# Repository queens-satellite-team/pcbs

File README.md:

# QSAT PCB Files

## Overview
This README contains information on how to setup your KiCad 6.0 environment. It includes:
1. How to use the existing schematic symbols and layout footprints
2. How to start a new project from an existing template
3. How to prepare the manufacturing and assembly files for ordering from JLCPCB

## Using QSAT PCB Symbols and Footprints

Following the instructions provided here: [How to Import into KiCad v6](https://support.snapeda.com/en/articles/5995733-how-to-import-into-kicad-v6-later)

**Import Symbols**

1. In KiCad, go to Preferences.

2. Click on Manage Symbol Libraries.

3. On the Global Libraries tab, click on Browse Libraries (the small folder icon below) 

4. Select the .lib file, then click Open. 

5. The library will appear, click OK.

6. Click on Symbol Editor.

7. Type on the filter search field, and navigate to the symbol you imported. Double-click over it to open the file.

**Import Footprints**

Using the *.kicad_mod file:

1. In KiCad, go to Preferences.

2. Click on Manage Footprint Libraries.

3. On the Global Libraries tab, click on Browse Libraries (the small folder icon below) 

4. Navigate to the Folder of the downloaded .kicad_mod file. Then click Select Folder. 

5. The library will appear, click OK. 

6. Click on Footprint Editor.

7. Type on the filter search field, and navigate to the footprint you imported. Double-click over it to open the file.

## Using QSAT PCB Templates

Following the instructions provided here: [KiCad Creating Templates](https://docs.kicad.org/5.1/en/kicad/kicad.html#creating_templates) we must:

1. Update our path configurations in KiCad to include the template folder.

a. Go to *Preferences* -> *Configure Paths* in the KiCad GUI.

b. Go to *KICAD_USER_TEMPLATE_DIR* and double click the path name until a folder apprears. 

c. Navigate to the *QSAT/pcbs/qsat-templates* directory and hit *Select Folder*

2. Create a new project from the template. 

a. Go to *File* -> *New Project From Template...* in the KiCad GUI.

b. Select the *User Templates* tab, and choose the template you want. 

**Note:** If starting a project from scratch it is recommended to use the *QSAT - PC104 Base Board* 
This is designed to have the same pcb footprint as the Clyde Space EPS board with mounting holes and
a PC104 connector.

## Ordering From JLCPCB

JLC has provided instructions for their required procedure, and is well detailed. 

The steps to generate the manufacturing files are found [here](https://support.jlcpcb.com/article/194-how-to-generate-gerber-and-drill-files-in-kicad-6). 

And the steps to generate the BOM and Centroid files are found [here](https://support.jlcpcb.com/article/84-how-to-generate-the-bom-and-centroid-file-from-kicad).

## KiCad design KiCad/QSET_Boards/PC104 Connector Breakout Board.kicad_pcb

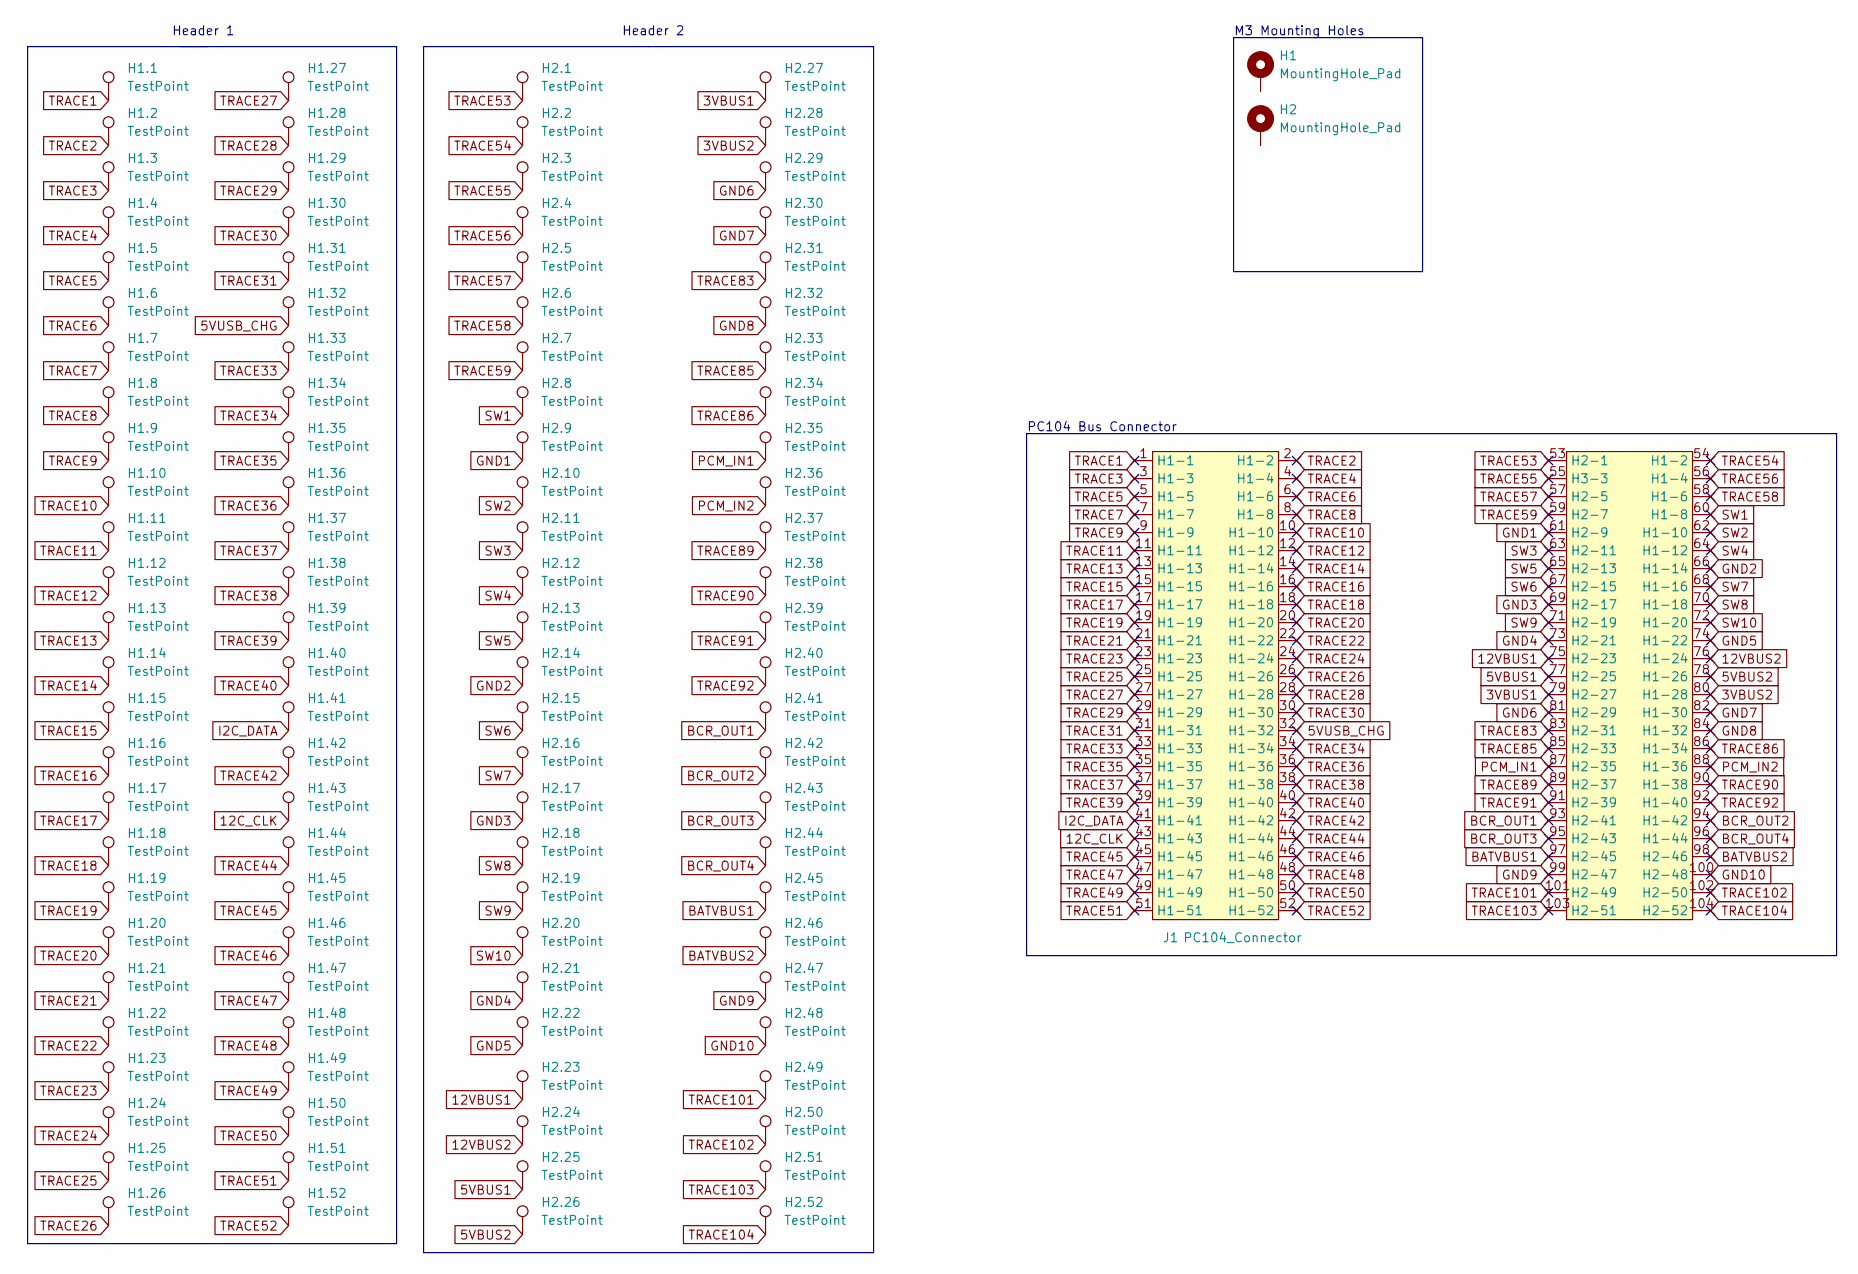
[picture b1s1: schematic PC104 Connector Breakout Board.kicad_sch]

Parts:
H1, H2: MountingHole_Pad; MountingHole_3.2mm_M3_Pad_TopBottom
H1.1, H1.2, H1.3, H1.4, H1.5, H1.6, H1.7, H1.8, H1.9, H1.10, H1.11, H1.12, H1.13, H1.14, H1.15, H1.16, H1.17, H1.18, H1.19, H1.20, H1.21, H1.22, H1.23, H1.24, H1.25, H1.26, H1.27, H1.28, H1.29, H1.30, H1.31, H1.32, H1.33, H1.34, H1.35, H1.36, H1.37, H1.38, H1.39, H1.40, H1.41, H1.42, H1.43, H1.44, H1.45, H1.46, H1.47, H1.48, H1.49, H1.50, H1.51, H1.52, H2.1, H2.2, H2.3, H2.4, H2.5, H2.6, H2.7, H2.8, H2.9, H2.10, H2.11, H2.12, H2.13, H2.14, H2.15, H2.16, H2.17, H2.18, H2.19, H2.20, H2.21, H2.22, H2.23, H2.24, H2.25, H2.26, H2.27, H2.28, H2.29, H2.30, H2.31, H2.32, H2.33, H2.34, H2.35, H2.36, H2.37, H2.38, H2.39, H2.40, H2.41, H2.42, H2.43, H2.44, H2.45, H2.46, H2.47, H2.48, H2.49, H2.50, H2.51, H2.52: TestPoint; TestPoint_Keystone_5000-5004_Miniature
J1: PC104_Connector; pc104-connector

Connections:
3VBUS1: H2.27.1, J1.79 (H2-27)
3VBUS2: H2.28.1, J1.80 (H1-28)
5VBUS1: H2.25.1, J1.77 (H2-25)
5VBUS2: H2.26.1, J1.78 (H1-26)
5VUSB_CHG: H1.32.1, J1.32 (H1-32)
12C_CLK: H1.43.1, J1.43 (H1-43)
12VBUS1: H2.23.1, J1.75 (H2-23)
12VBUS2: H2.24.1, J1.76 (H1-24)
BATVBUS1: H2.45.1, J1.97 (H2-45)
BATVBUS2: H2.46.1, J1.98 (H2-46)
BCR_OUT1: H2.41.1, J1.93 (H2-41)
BCR_OUT2: H2.42.1, J1.94 (H1-42)
BCR_OUT3: H2.43.1, J1.95 (H2-43)
BCR_OUT4: H2.44.1, J1.96 (H1-44)
GND1: H2.9.1, J1.61 (H2-9)
GND2: H2.14.1, J1.66 (H1-14)
GND3: H2.17.1, J1.69 (H2-17)
GND4: H2.21.1, J1.73 (H2-21)
GND5: H2.22.1, J1.74 (H1-22)
GND6: H2.29.1, J1.81 (H2-29)
GND7: H2.30.1, J1.82 (H1-30)
GND8: H2.32.1, J1.84 (H1-32)
GND9: H2.47.1, J1.99 (H2-47)
GND10: H2.48.1, J1.100 (H2-48)
I2C_DATA: H1.41.1, J1.41 (H1-41)
PCM_IN1: H2.35.1, J1.87 (H2-35)
PCM_IN2: H2.36.1, J1.88 (H1-36)
SW1: H2.8.1, J1.60 (H1-8)
SW2: H2.10.1, J1.62 (H1-10)
SW3: H2.11.1, J1.63 (H2-11)
SW4: H2.12.1, J1.64 (H1-12)
SW5: H2.13.1, J1.65 (H2-13)
SW6: H2.15.1, J1.67 (H2-15)
SW7: H2.16.1, J1.68 (H1-16)
SW8: H2.18.1, J1.70 (H1-18)
SW9: H2.19.1, J1.71 (H2-19)
SW10: H2.20.1, J1.72 (H1-20)
TRACE1: H1.1.1, J1.1 (H1-1)
TRACE2: H1.2.1, J1.2 (H1-2)
TRACE3: H1.3.1, J1.3 (H1-3)
TRACE4: H1.4.1, J1.4 (H1-4)
TRACE5: H1.5.1, J1.5 (H1-5)
TRACE6: H1.6.1, J1.6 (H1-6)
TRACE7: H1.7.1, J1.7 (H1-7)
TRACE8: H1.8.1, J1.8 (H1-8)
TRACE9: H1.9.1, J1.9 (H1-9)
TRACE10: H1.10.1, J1.10 (H1-10)
TRACE11: H1.11.1, J1.11 (H1-11)
TRACE12: H1.12.1, J1.12 (H1-12)
TRACE13: H1.13.1, J1.13 (H1-13)
TRACE14: H1.14.1, J1.14 (H1-14)
TRACE15: H1.15.1, J1.15 (H1-15)
TRACE16: H1.16.1, J1.16 (H1-16)
TRACE17: H1.17.1, J1.17 (H1-17)
TRACE18: H1.18.1, J1.18 (H1-18)
TRACE19: H1.19.1, J1.19 (H1-19)
TRACE20: H1.20.1, J1.20 (H1-20)
TRACE21: H1.21.1, J1.21 (H1-21)
TRACE22: H1.22.1, J1.22 (H1-22)
TRACE23: H1.23.1, J1.23 (H1-23)
TRACE24: H1.24.1, J1.24 (H1-24)
TRACE25: H1.25.1, J1.25 (H1-25)
TRACE26: H1.26.1, J1.26 (H1-26)
TRACE27: H1.27.1, J1.27 (H1-27)
TRACE28: H1.28.1, J1.28 (H1-28)
TRACE29: H1.29.1, J1.29 (H1-29)
TRACE30: H1.30.1, J1.30 (H1-30)
TRACE31: H1.31.1, J1.31 (H1-31)
TRACE33: H1.33.1, J1.33 (H1-33)
TRACE34: H1.34.1, J1.34 (H1-34)
TRACE35: H1.35.1, J1.35 (H1-35)
TRACE36: H1.36.1, J1.36 (H1-36)
TRACE37: H1.37.1, J1.37 (H1-37)
TRACE38: H1.38.1, J1.38 (H1-38)
TRACE39: H1.39.1, J1.39 (H1-39)
TRACE40: H1.40.1, J1.40 (H1-40)
TRACE42: H1.42.1, J1.42 (H1-42)
TRACE44: H1.44.1, J1.44 (H1-44)
TRACE45: H1.45.1, J1.45 (H1-45)
TRACE46: H1.46.1, J1.46 (H1-46)
TRACE47: H1.47.1, J1.47 (H1-47)
TRACE48: H1.48.1, J1.48 (H1-48)
TRACE49: H1.49.1, J1.49 (H1-49)
TRACE50: H1.50.1, J1.50 (H1-50)
TRACE51: H1.51.1, J1.51 (H1-51)
TRACE52: H1.52.1, J1.52 (H1-52)
TRACE53: H2.1.1, J1.53 (H2-1)
TRACE54: H2.2.1, J1.54 (H1-2)
TRACE55: H2.3.1, J1.55 (H3-3)
TRACE56: H2.4.1, J1.56 (H1-4)
TRACE57: H2.5.1, J1.57 (H2-5)
TRACE58: H2.6.1, J1.58 (H1-6)
TRACE59: H2.7.1, J1.59 (H2-7)
TRACE83: H2.31.1, J1.83 (H2-31)
TRACE85: H2.33.1, J1.85 (H2-33)
TRACE86: H2.34.1, J1.86 (H1-34)
TRACE89: H2.37.1, J1.89 (H2-37)
TRACE90: H2.38.1, J1.90 (H1-38)
TRACE91: H2.39.1, J1.91 (H2-39)
TRACE92: H2.40.1, J1.92 (H1-40)
TRACE101: H2.49.1, J1.101 (H2-49)
TRACE102: H2.50.1, J1.102 (H2-50)
TRACE103: H2.51.1, J1.103 (H2-51)
TRACE104: H2.52.1, J1.104 (H2-52)

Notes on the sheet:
M3 Mounting Holes
Header 2
Header 1
PC104 Bus Connector

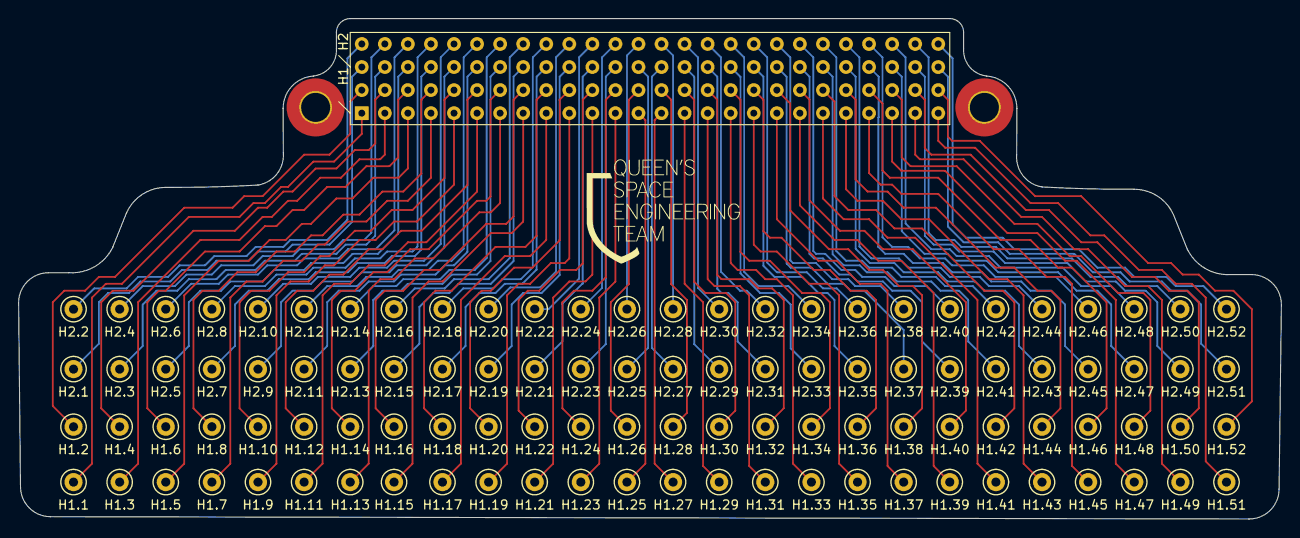
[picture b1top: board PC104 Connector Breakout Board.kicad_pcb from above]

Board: 2 copper layers, 139.1 x 55.1 mm, 107 parts (0 on the bottom side), 104 nets.

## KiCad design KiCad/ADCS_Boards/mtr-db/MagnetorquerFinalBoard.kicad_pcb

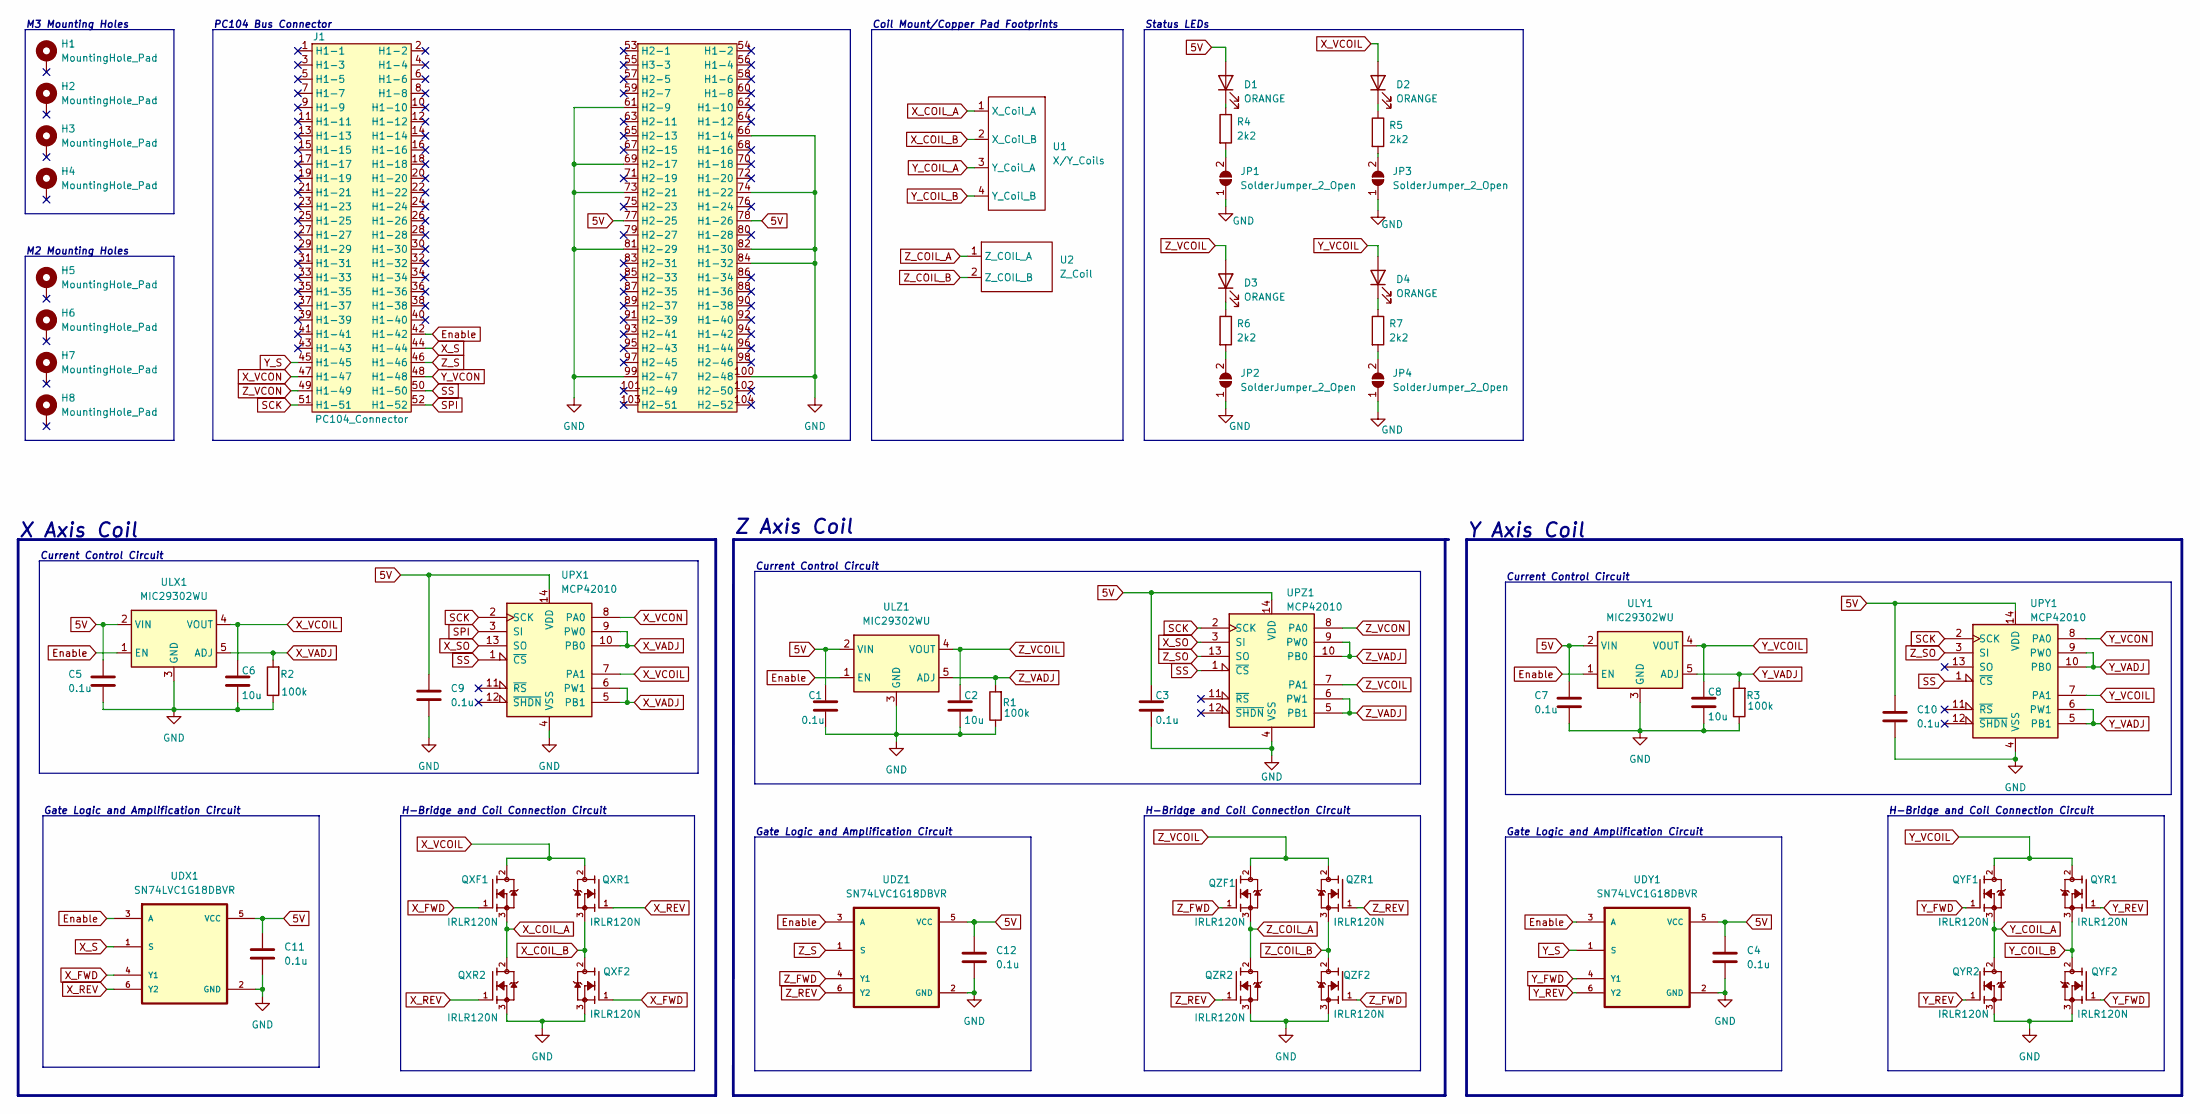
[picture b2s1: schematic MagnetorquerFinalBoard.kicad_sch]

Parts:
C1, C3, C4, C5, C7, C9, C10, C11, C12: 0.1u; C_0603_1608Metric
C2, C6, C8: 10u; C_0603_1608Metric
D1, D2, D3, D4: ORANGE; LED_0603_1608Metric
H1, H2, H3, H4: MountingHole_Pad; MountingHole_3.2mm_M3_Pad_TopBottom
H5, H6, H7, H8: MountingHole_Pad; MountingHole_2.2mm_M2_Pad_TopBottom
J1: PC104_Connector; pc104-connector
JP1, JP2, JP3, JP4: SolderJumper_2_Open; SolderJumper-2_P1.3mm_Open_TrianglePad1.0x1.5mm
QXF1, QXF2: IRLR120N; TO-252-2; PARTREV july 2014
QXR1, QXR2: IRLR120N; TO-252-2; PARTREV july 2014
QYF1, QYF2: IRLR120N; TO-252-2; PARTREV july 2014
QYR1, QYR2: IRLR120N; TO-252-2; PARTREV july 2014
QZF1, QZF2: IRLR120N; TO-252-2; PARTREV july 2014
QZR1, QZR2: IRLR120N; TO-252-2; PARTREV july 2014
R1, R2, R3: 100k; R_0603_1608Metric
R4, R5, R6, R7: 2k2; R_0603_1608Metric
U1: X/Y_Coils; Front Coils Mount
U2: Z_Coil; ZCoil
UDX1: SN74LVC1G18DBVR; SOT95P280X145-6N
UDY1: SN74LVC1G18DBVR; SOT95P280X145-6N
UDZ1: SN74LVC1G18DBVR; SOT95P280X145-6N
ULX1: MIC29302WU; TO-263-5_TabPin3
ULY1: MIC29302WU; TO-263-5_TabPin3
ULZ1: MIC29302WU; TO-263-5_TabPin3
UPX1: MCP42010; SOIC127P600X175-14N
UPY1: MCP42010; SOIC127P600X175-14N
UPZ1: MCP42010; SOIC127P600X175-14N

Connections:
5V: C1.1, C3.1, C4.1, C5.1, C7.1, C9.1, C10.1, C11.1, C12.1, D1.2 (A), J1.77 (H2-25), J1.78 (H1-26), UDX1.5 (VCC), UDY1.5 (VCC), UDZ1.5 (VCC), ULX1.2 (VIN), ULY1.2 (VIN), ULZ1.2 (VIN), UPX1.14 (VDD), UPY1.14 (VDD), UPZ1.14 (VDD)
Enable: J1.42 (H1-42), UDX1.3 (A), UDY1.3 (A), UDZ1.3 (A), ULX1.1 (EN), ULY1.1 (EN), ULZ1.1 (EN)
GND: C1.2, C2.2, C3.2, C4.2, C5.2, C6.2, C7.2, C8.2, C9.2, C10.2, C11.2, C12.2, J1.61 (H2-9), J1.66 (H1-14), J1.69 (H2-17), J1.73 (H2-21), J1.74 (H1-22), J1.81 (H2-29), J1.82 (H1-30), J1.84 (H1-32), J1.99 (H2-47), J1.100 (H2-48), JP1.1 (A), JP2.1 (A), JP3.1 (A), JP4.1 (A), QXF2.3, QXR2.3, QYF2.3, QYR2.3, QZF2.3, QZR2.3, R1.1, R2.1, R3.1, UDX1.2 (GND), UDY1.2 (GND), UDZ1.2 (GND), ULX1.3 (GND), ULY1.3 (GND), ULZ1.3 (GND), UPX1.4 (VSS), UPY1.4 (VSS), UPZ1.4 (VSS)
unnamed: D1.1 (K), R4.1
unnamed: D2.1 (K), R5.1
unnamed: D3.1 (K), R6.1
unnamed: D4.1 (K), R7.1
unnamed: JP1.2 (B), R4.2
unnamed: JP3.2 (B), R5.2
unnamed: JP2.2 (B), R6.2
unnamed: JP4.2 (B), R7.2
SCK: J1.51 (H1-51), UPX1.2 (SCK), UPY1.2 (SCK), UPZ1.2 (SCK)
SPI: J1.52 (H1-52), UPX1.3 (SI)
SS: J1.50 (H1-50), UPX1.1 (~CS), UPY1.1 (~CS), UPZ1.1 (~CS)
X_COIL_A: QXF1.3, QXR2.2, U1.1 (X_Coil_A)
X_COIL_B: QXF2.2, QXR1.3, U1.2 (X_Coil_B)
X_FWD: QXF1.1, QXF2.1, UDX1.4 (Y1)
X_REV: QXR1.1, QXR2.1, UDX1.6 (Y2)
X_S: J1.44 (H1-44), UDX1.1 (S)
X_SO: UPX1.13 (SO), UPZ1.3 (SI)
X_VADJ: R2.2, ULX1.5 (ADJ), UPX1.5 (PB1), UPX1.6 (PW1), UPX1.9 (PW0), UPX1.10 (PB0)
X_VCOIL: C6.1, D2.2 (A), QXF1.2, QXR1.2, ULX1.4 (VOUT), UPX1.7 (PA1)
X_VCON: J1.47 (H1-47), UPX1.8 (PA0)
Y_COIL_A: QYF1.3, QYR2.2, U1.3 (Y_Coil_A)
Y_COIL_B: QYF2.2, QYR1.3, U1.4 (Y_Coil_B)
Y_FWD: QYF1.1, QYF2.1, UDY1.4 (Y1)
Y_REV: QYR1.1, QYR2.1, UDY1.6 (Y2)
Y_S: J1.45 (H1-45), UDY1.1 (S)
Y_VADJ: R3.2, ULY1.5 (ADJ), UPY1.5 (PB1), UPY1.6 (PW1), UPY1.9 (PW0), UPY1.10 (PB0)
Y_VCOIL: C8.1, D4.2 (A), QYF1.2, QYR1.2, ULY1.4 (VOUT), UPY1.7 (PA1)
Y_VCON: J1.48 (H1-48), UPY1.8 (PA0)
Z_COIL_A: QZF1.3, QZR2.2, U2.1 (Z_COIL_A)
Z_COIL_B: QZF2.2, QZR1.3, U2.2 (Z_COIL_B)
Z_FWD: QZF1.1, QZF2.1, UDZ1.4 (Y1)
Z_REV: QZR1.1, QZR2.1, UDZ1.6 (Y2)
Z_S: J1.46 (H1-46), UDZ1.1 (S)
Z_SO: UPY1.3 (SI), UPZ1.13 (SO)
Z_VADJ: R1.2, ULZ1.5 (ADJ), UPZ1.5 (PB1), UPZ1.6 (PW1), UPZ1.9 (PW0), UPZ1.10 (PB0)
Z_VCOIL: C2.1, D3.2 (A), QZF1.2, QZR1.2, ULZ1.4 (VOUT), UPZ1.7 (PA1)
Z_VCON: J1.49 (H1-49), UPZ1.8 (PA0)

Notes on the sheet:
M3 Mounting Holes
Gate Logic and Amplification Circuit
M2 Mounting Holes
Status LEDs
Z Axis Coil
X Axis Coil
Current Control Circuit
Y Axis Coil
PC104 Bus Connector
H-Bridge and Coil Connection Circuit
Coil Mount/Copper Pad Footprints

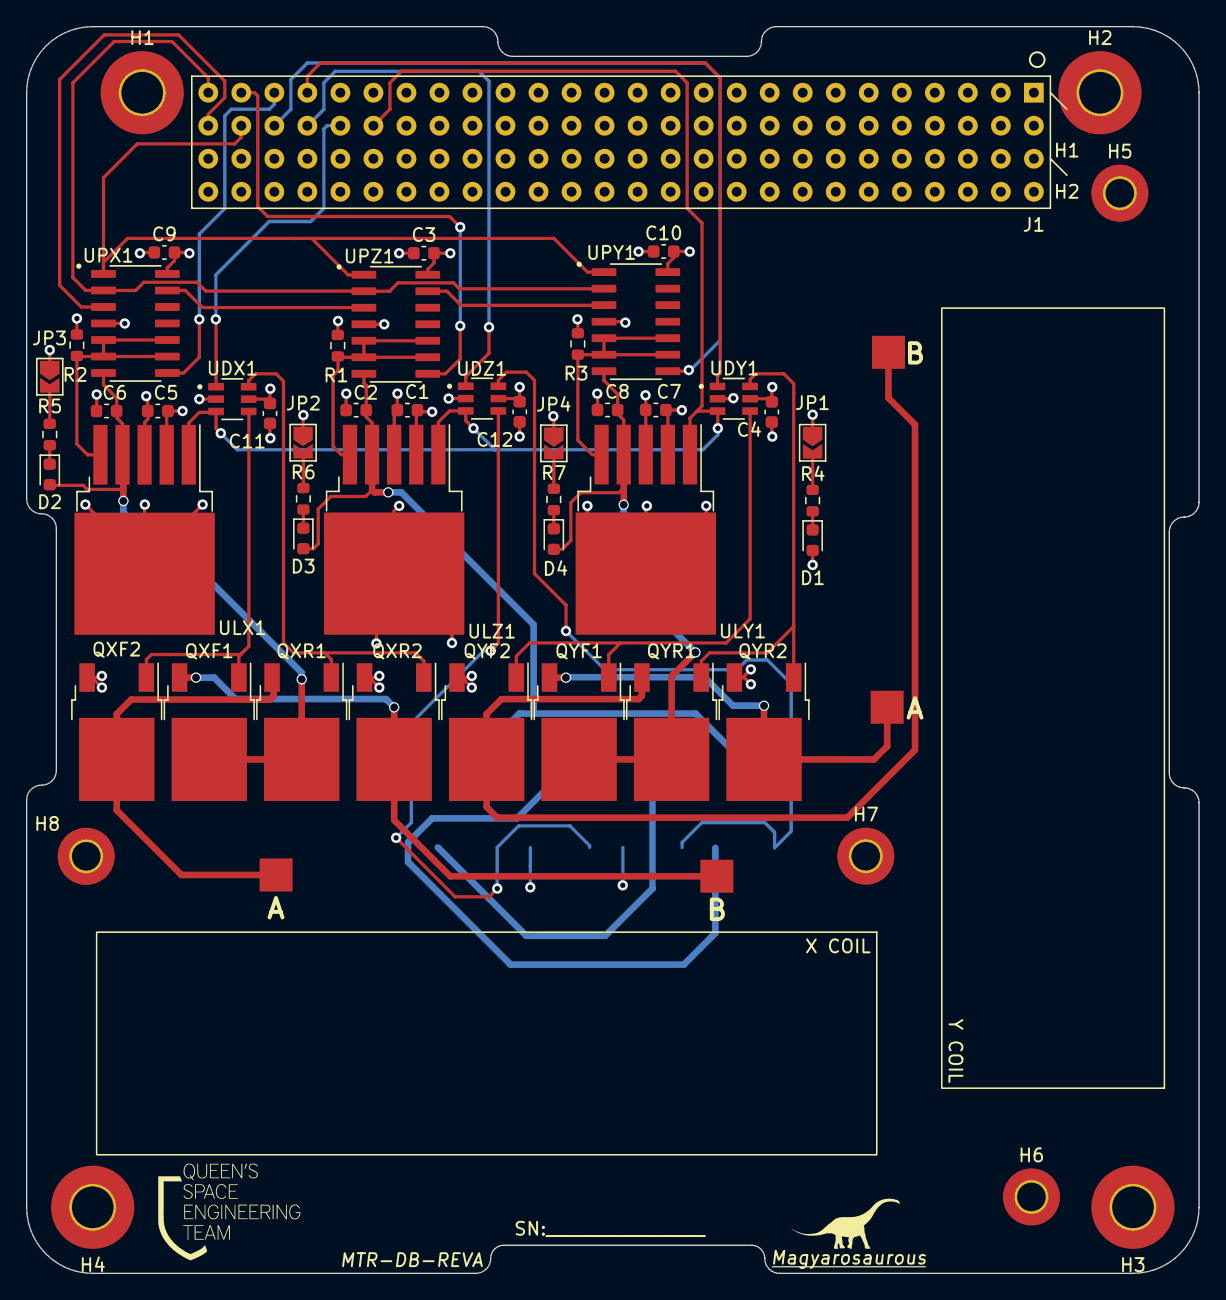
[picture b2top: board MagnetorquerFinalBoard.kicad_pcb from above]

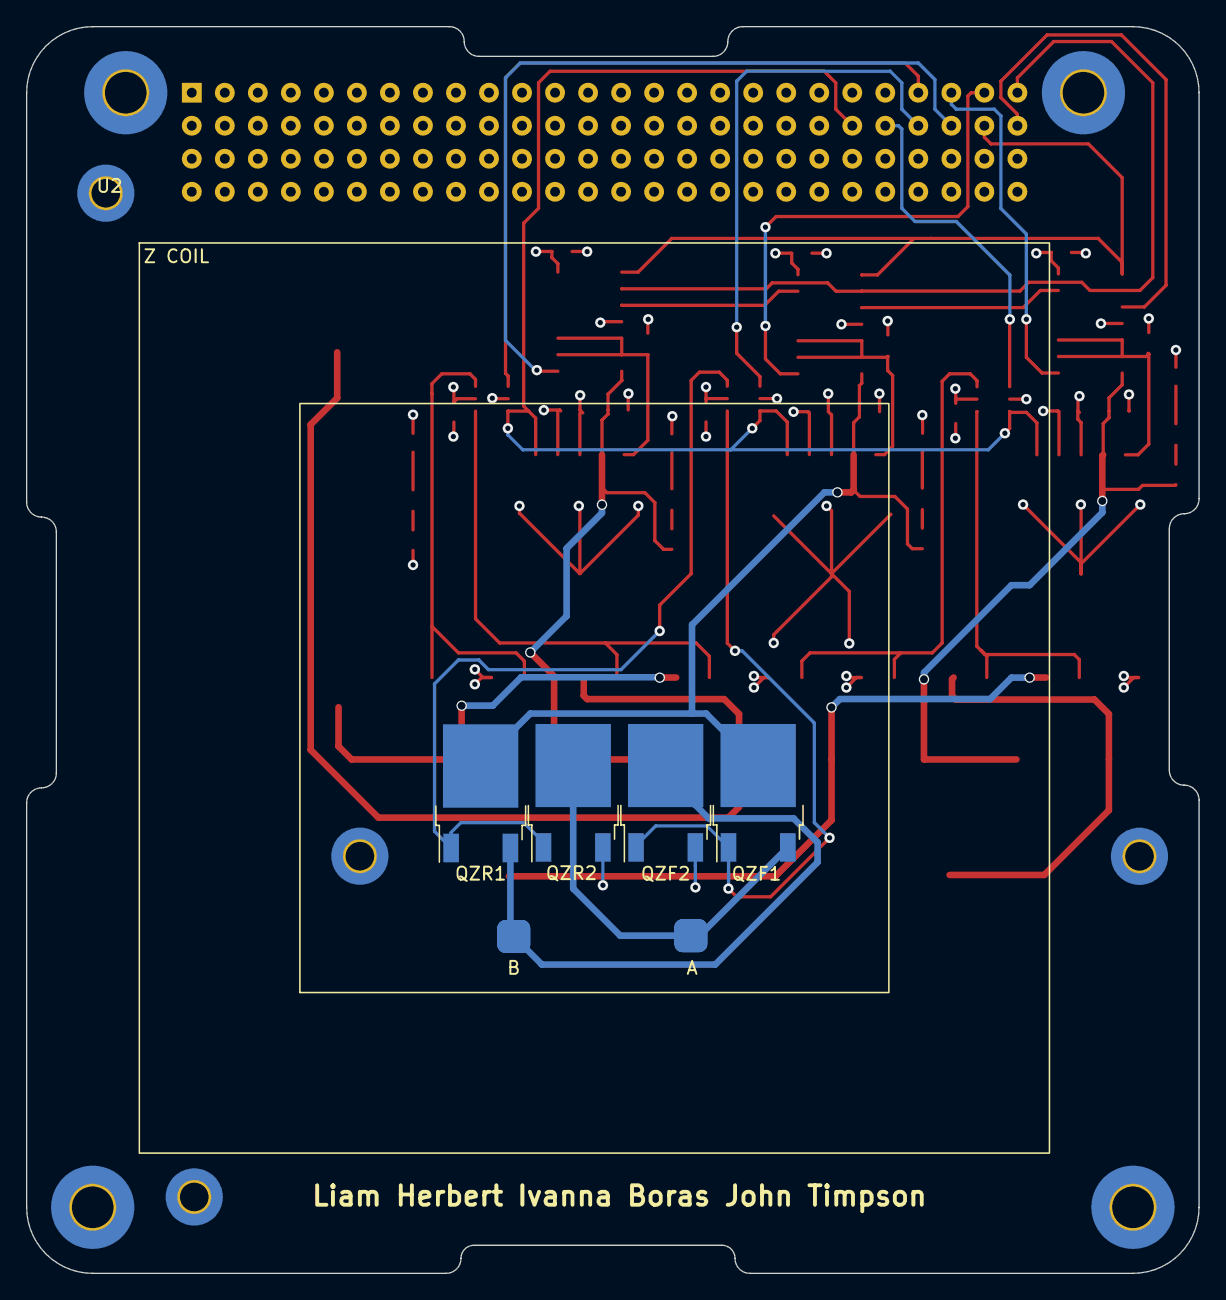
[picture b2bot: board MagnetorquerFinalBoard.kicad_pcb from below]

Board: 4 copper layers, 90.2 x 95.9 mm, 59 parts (5 on the bottom side), 40 nets.

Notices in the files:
parts and their libraries:
Copyright 2021 Accelerated Designs. All rights reserved.
